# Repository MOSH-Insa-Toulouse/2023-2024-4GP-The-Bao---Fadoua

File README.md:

# 2023-2024-4GP-The-Bao---Fadoua

# 1. Description du projet  
Notre projet, inscrit dans l'UF "Du capteur au banc de test en open source hardware" de la 4ème année de Génie Physique à l’INSA Toulouse, vise à concevoir, fabriquer et caractériser un capteur de contrainte innovant utilisant une approche low-tech basée sur des capteurs en graphite. S'inspirant des travaux de chercheurs dans le domaine des capteurs, notre objectif est de développer un système de mesure complet, intégrant un shield Arduino avec un circuit analogique incluant un amplificateur transimpédance et des filtres, ainsi qu'une interface utilisateur via un écran OLED et une communication sans fil avec une application Android via un module Bluetooth. Nous avons également créé un banc de test pour évaluer les performances du capteur, en mesurant sa variation de résistance en fonction de la déformation induite par différents crayons graphites. Ces travaux aboutiront à la rédaction d'une datasheet détaillée du capteur, offrant ainsi une solution open source pour la mesure de contraintes basée sur une approche low-tech.

# 2. Livrables 
Les livrables de ce projet sont les suivants :
  
* Circuit Shield PCB avec Arduino UNO
     
   - Schéma électrique du circuit amplificateur transimpédance
   - Conception du PCB réalisée sous KiCad
   - Fabrication du PCB et soudure des composants
   - Intégration des éléments : amplificateur, module Bluetooth, écran OLED, encodeur rotatif
  
* Code Arduino     
   - Développement complet d'un code Arduino pour le fonctionnement du système.
   -  Fonctionnalités incluses :
   - Mesure de la déformation du capteur à base de graphite.
   -Transmission des données via le module Bluetooth.
   - Affichage des mesures sur l'écran OLED.
   - Utilisation de l'encodeur rotatif pour naviguer dans le menu de l'OLED.
  
* Application Android (APK)
* Banc de Test Dédié au Capteur
*  Datasheet Complète du Capteur
 ## 3. Matériel nécessaire
* Carte Arduino UNO
* Amplificateur opérationnel (LTC1050)
* Module Bluetooth (HC-05)
* Écran OLED
* Encodeur rotatif (KY-040)
* Flex Sensor
* 2 Résistance de 100kΩ
* 1 Résistance de 1kΩ
* 1 Résistance de 10kΩ
* Potentiomètre digital MCP-41050
* 2 Condensateurs 100nF
* 1 Condensateurs 1µF

 # 4. Electronique Analogique:
 
Le circuit amplificateur transimpédance est une composante essentielle de notre projet, car il permet de convertir le courant provenant du capteur de déformation à base de graphite en une tension mesurable. Composé de plusieurs éléments interagissant de manière précise, ce circuit garantit des mesures fiables et précises tout au long du processus.

Au cœur du circuit se trouve l'amplificateur opérationnel LTC1050, auquel le capteur de déformation est connecté à l'entrée inverseuse. Ce capteur, conçu pour ajuster sa résistance en fonction de la déformation, induit ainsi un changement de courant à travers la résistance de rétroaction R1.

La précision de nos mesures est assurée par le choix du LTC1050 pour ses faibles valeurs d'offset et de dérive. En complément, nous avons intégré trois étages de filtres au circuit pour optimiser le signal. Un filtre passe-bas à l'entrée (R1,C1) de 16 Hz atténue les hautes fréquences indésirables. Un second filtre passe-bas (R4, C2) de 1,6 Hz élimine le bruit de 50 Hz du réseau électrique. Enfin, un filtre final (R5,C3) de 1,6 kHz traite le bruit de l'ADC pour garantir des mesures précises et stables.

Chaque composant du circuit a été soigneusement sélectionné et dimensionné pour optimiser les performances. Des simulations approfondies sous LTSpice ont validé le fonctionnement du circuit avant la conception du PCB final. Des tests sur une breadboard ont confirmé sa fiabilité en conditions réelles, avec des mesures de résistance et de déformation du capteur réalisées pour évaluer sa précision.

La formule utilisée pour calculer la résistance du capteur de contrainte au graphite est la suivante :

      𝑅𝑠𝑒𝑛𝑠𝑜𝑟 = (1 +𝑅4/𝑅2) ∗ 𝑅1 ∗ (𝑉𝐶𝐶/𝑉𝐴𝐷𝐶) − 𝑅1 − 𝑅3

<h2> Modélisation du capteur:
     
</br>

<h2> Voici le schéma du circuit simulé sur le logiciel LTSpice :

</br>

 # 5. Progamme Arduino:
 Notre programme d'Arduino nous permet de mesurer la résistance des deux capteurs (Flex sensor et Capteur en graphine) à partir de la valeur tension mesuré par la composant ADC dans l'Arduino. Il affiche ensuite sur l'écran OLED les valeurs de résistance sélectionnées en tournant l'encodeur rotatoire. 

Dans notre programme, on a également établi la connexion entre la module bluetooth et l'application mobile. C'est à dire qu'on a créé les protocols de communication entre eux. Vous pouvez voir dans le diagramme ci-dessous que le module Bluetooth est utilisé pour recevoir les commandes de l'application mobile et lui envoyer les données demandées. L'Arduino va recevoir ces commandes pour envoyer des données à l'application mobile ou régler la résistance du potentiomètre numérique afin de changer le gain de l'amplificateur. 

 # 6. KiCad:
 ## Réalisation de la Schématique de Shield
Dans cette étape de réalisation de la schématique du shield, notre objectif principal était de concevoir un circuit électronique fonctionnel pour notre projet. Nous avons choisi le logiciel KiCad comme plateforme de conception et nous nous sommes basés sur le modèle d'une carte Arduino Uno pour assurer la compatibilité. Après avoir identifié tous les composants nécessaires pour notre projet, nous avons ensuite procédé à la création de notre propre bibliothèque d'empreintes personnalisées pour les composants manquants. Cette démarche nous a permis d'adapter notre conception à nos besoins spécifiques et d'assurer une intégration optimale des composants dans notre schéma électrique.
Voici les symboles et empreintes des composants que nous avons créés dans le logiciel KiCad :

### **Module Bluetooth (HC-05)**
  
<div class="column" align="center">

</div>

### **Encodeur rotatif (KY-040)**
<div class="column" align="center">

</div>

### **Écran OLED**
<div class="column" align="center"> 

</div>

### **Flex Sensor**
  <div class="column" align="center">

</div>

###  **Potentiomètre digital MCP-41050**

<div class="column" align="center">

</div>

Après avoir créé les schémas et les empreintes pour chaque composant, nous avons assemblé le schéma électrique complet du shield Arduino en reliant les broches des composants avec celles de la carte Arduino.

<div class="column" align="center">

</div>

### Réalisation de la Schématique du PCB et visualisation 3D
Dans cette étape, nous avons réalisé le routage de notre circuit en intégrant les composants sur le PCB, tout en veillant à limiter les distances entre les composants et leurs pins, conformément aux directives de nos enseignants référents, M. Jérémie Grisolia et Mme Catherine Crouzet. Nous avons respecté des paramètres spécifiques tels que la largeur des pistes, la largeur d'isolation des pistes et les dimensions des trous pour chaque composant, afin d'assurer la conformité de notre conception. Une fois cette phase terminée, nous avons ajouté le plan de masse pour relier les pistes au GND.

Les paramètres spécifiques suivants ont été respectés :
* Taille du trou de perçage pour l'écran OLED,Flex Sensor,le module Bluetooth et l'encodeur rotatoire, l'AOP et le potentiomètre digital = 1mm
* Taille du trou de perçage pour les résistances et les capacités = 0.8 mm
* Dimensions du trou pour le support de l'AOP ,l'écran OLED,Flex Sensor,le module Bluetooth et l'encodeur rotatoire,le potentiomètre digital (pad n°1 rectangulaire et les autres pins sont ovales) = 2 mm * 2.5 mm
* Largeur d'isolation des pistes = 0.8 mm
* Taille du trou de perçage du via = 0.8 mm

### **Visualisation 3D**
  
Après avoir réalisé le PCB, le téléchargement des modèles de composants sur le site "grabcad.com", qui n'étaient pas fournis par KiCad, s'est avéré très utile. Cela nous a permis d'obtenir un modèle 3D de notre PCB final. Nous avons ainsi pu vérifier que les positions des composants étaient correctes avant de passer à l'étape de l'impression du circuit.

### **Fabrication du shield PCB:**
  
Dans le cadre de notre projet, nous avons fabriqué un circuit imprimé (PCB) au sein des départements de Génie Électrique et Informatique et de Génie Physique de l'INSA Toulouse. La fabrication a commencé par la modélisation du circuit sur le logiciel KICAD, suivie de l'impression de cette modélisation sur du papier calque. Nous avons ensuite réalisé une insolation UV de notre plaquette d’époxy recouverte d’une fine couche de cuivre (environ 60 µm) pendant une dizaine de minutes, en utilisant le calque comme masque. La résine non exposée aux UV a été retirée avec un révélateur, puis la plaquette a été plongée dans un bain de perchlorure de fer pendant environ 7 à 9 minutes. Cette étape a permis de dissoudre le cuivre non protégé et de révéler les pistes du circuit. Enfin, un rinçage à l'acétone a été effectué pour éliminer les dernières traces de résine, nous permettant ainsi d'obtenir notre PCB conforme à la modélisation initiale. Cette réalisation a été possible grâce à l'aide précieuse de Cathy, assurant la qualité et la précision du produit final.

<div class="column" align="center">

 </div>

### Assemblage des composantes :
Une fois le PCB fabriqué, nous avons procédé à l'assemblage des composants, ce qui implique le perçage du PCB et la soudure des éléments électroniques. Conformément aux spécifications de notre projet, deux tailles de trous ont été prévues dans la conception sur KICAD : des trous de 0,8 mm de diamètre pour les composants tels que les amplificateurs opérationnels (AOP) LTC1050, les résistances et les capacités, et des trous de 1 mm de diamètre pour les broches de connexion de la carte Arduino Uno et les headers des différents modules (OLED, Bluetooth, encodeur rotatif...). À l'aide d'une perceuse électrique, nous avons percé le PCB aux emplacements désignés pour insérer les composants. Ensuite, nous avons soudé les composants en place en utilisant de l'étain pour assurer des connexions électriques solides et fiables. Ce processus d'assemblage a permis d'obtenir un shield opérationnel, prêt à être intégré dans notre système.

<div class="column" align="center">

</div>

 # 7. Application mobile:
Pour ce projet, nous avons développé une application mobile sur MIT App Inventor qui se connecte au module Bluetooth du capteur. Cette application dispose d'une interface unique permettant d'acquérir les données du capteur en temps réel, de les visualiser sur un graphique dynamique et de enregistrer le graphique dans notre téléphone ainsi que de régler le gain de l'amplificateur.

# Initilisation de programme:
<h3>Au début, nous avons déclaré les variable globale utilisé dans le programme de l'application

<br />

Initialiser le programme 

# Composantes dans l'interface:
## "Connect Device" 

Ce bouton est utilisé pour choisir la module bluetooth qu'on veut le connecter

## Statut de connexion bluetooth:
Étiquette représentant la statut de connexion Bluetooth. 

## "Disconnect" 
 Ce bouton est utilisé pour déconnecter la bluetooth.

## Zone graphique
 
On a utilisé la composante "Canvas" dans MIT pour visualiser le signal

Dans cette zone, le signal de tension mesuré est visualisé en fonction du temps. Chaque fois que le potentiel est mesuré, il est représenté par un point sur le graphique.

Concernant le fond du graphique, il est représenté en échelle linéaire. Chaque petit carré correspond à 500 ms en horizontale et à 0,25 V en verticale.

Figure 3: Le fond de la graphique

## Statut "Overload"

Parce que, l'Arduino ne mesure que jusqu'à 5V. En outre, avec un gain variable d'ampificatuer, la tension mesurée peut facilement devenir saturée. Ce phénomètre peut être observé lorsque le signal est visualisé dans la graphique. Pourtant, si on prendla valeur de résistance en seul fois, la saturation causerait un mal calcul de la résistance de capteur

Dans notre programme d'Arduino, nous avons défini une limitation de tension mesurée pour éviter la sarturation. La limitation de tension est 0 - 4.8V. Pour pouvoir détecter la saturation, une fois que la tension mesurée dépasse cette limite, l'Arduino vas envoyer un message qui contient une chaine des charactères "over". Si la message recus contien ce mot, l'étiquette "Overload" devient rouge; sinon, elle reste verte.

## "Start"
Lancer l'acquitiion de tension continue avec le délai entre deux acquisitions est 100ms

Une fois ce bouton est appuyé, il désactivera les boutons restants pour éviter d'être pressé par erreur et d'affecter l'acquisition. Pour arrêter l'acquisition, appuyez une nouvelle fois sur ce bouton.

Pour pouvoir récupérer automatiquement des données, nous commandons séquentiellement Arduino de nous evoyer les données. Pour cela, nous avons utilisé le composante "Clock"dans MIT

## "Step"
Ce bouton sert à récupérer la valeur de résistance du capteur sélectionné en une seule fois.

## "Save graph"

"En appuyant sur ce bouton, nous pouvons enregistrer le graphique dans le dossier "Photos" de notre téléphone au format .png. Pour cela, au début, on sauvegarde le graphe dans une mémoire externe de téléphone et nous le déplacons dans la dossier Photos de téléphone à l'aide d'extention "Taifuntool" 

## "Flex sensor" et "Graphite"
Ces boutons permettent de choisir le capteur dont on veut afficher la valeur.

## "Gain" Slider
Il utilisé pour régler le gain de l'amplificateur en changant la résistance de potentiomètre numérique. En utilisant ce curseurs, on peut choisir le gain qu'on souhaite. 

## "Change gain"

Un fois qu'on appuie sur ce bouton, on envoie un commande à l'Arduino pour changer le gain de l'amplificateur

## "Resistance Potentiometre"

Ce bouton sert à lire la résistance de potentiomètre

## "File Name" 

Ce composante est utilisé pour nommer la graphe qu'on va sauvegarder

 # 8. Mesures et résultats :
 
Pour étudier les caractéristiques du capteur, nous avons utilisé un banc d'essai composé de sept demi-cylindres disposés de manière séquentielle, du plus petit au plus grand. Le diamètre de chaque demi-cylindre variait de 2 cm à 5 cm, avec un pas de 0,5 cm.

Notre objectif était d'analyser la résistance du capteur en fonction de sa déformation induite en le pliant sur ces cylindres. Le degré de déformation a été calculé à l'aide de la formule  
 
      𝜀 = 𝑒 / (2r) 

Où **𝜀** représente la déformation, **e** désigne l'épaisseur de la feuille de papier, et **r** représente le rayon de chaque demi-cylindre. Pour l'épaisseur **e**, nous avons choisi une valeur de 0,16 mm, correspondant au grammage d'une feuille avec une densité de 140 g/m². 

Notre expérimentation a consisté à mesurer la déformation des capteurs sous compression et sous tension afin d'évaluer de manière exhaustive leurs caractéristiques de performance.

# 9. Remerciement et contact

Nous souhaiterions remercier Catherine Crouzet qui nous a beaucoup aidé à comprendre et à solutionner nos problèmes tout au long du projet. Nous adressons également nos remerciements à Jérémie Grisolia et Arnaud Biganzoli pour leur aide à la programmation Arduino et Github. 

Pour toutes questions ou informations supplémentaires, vous pouvez nous contacter par mail :

The Bao PHAM: pha@insatoulouse.fr
Fadoua EL GOURARI : elgourar@insa-toulouse.fr

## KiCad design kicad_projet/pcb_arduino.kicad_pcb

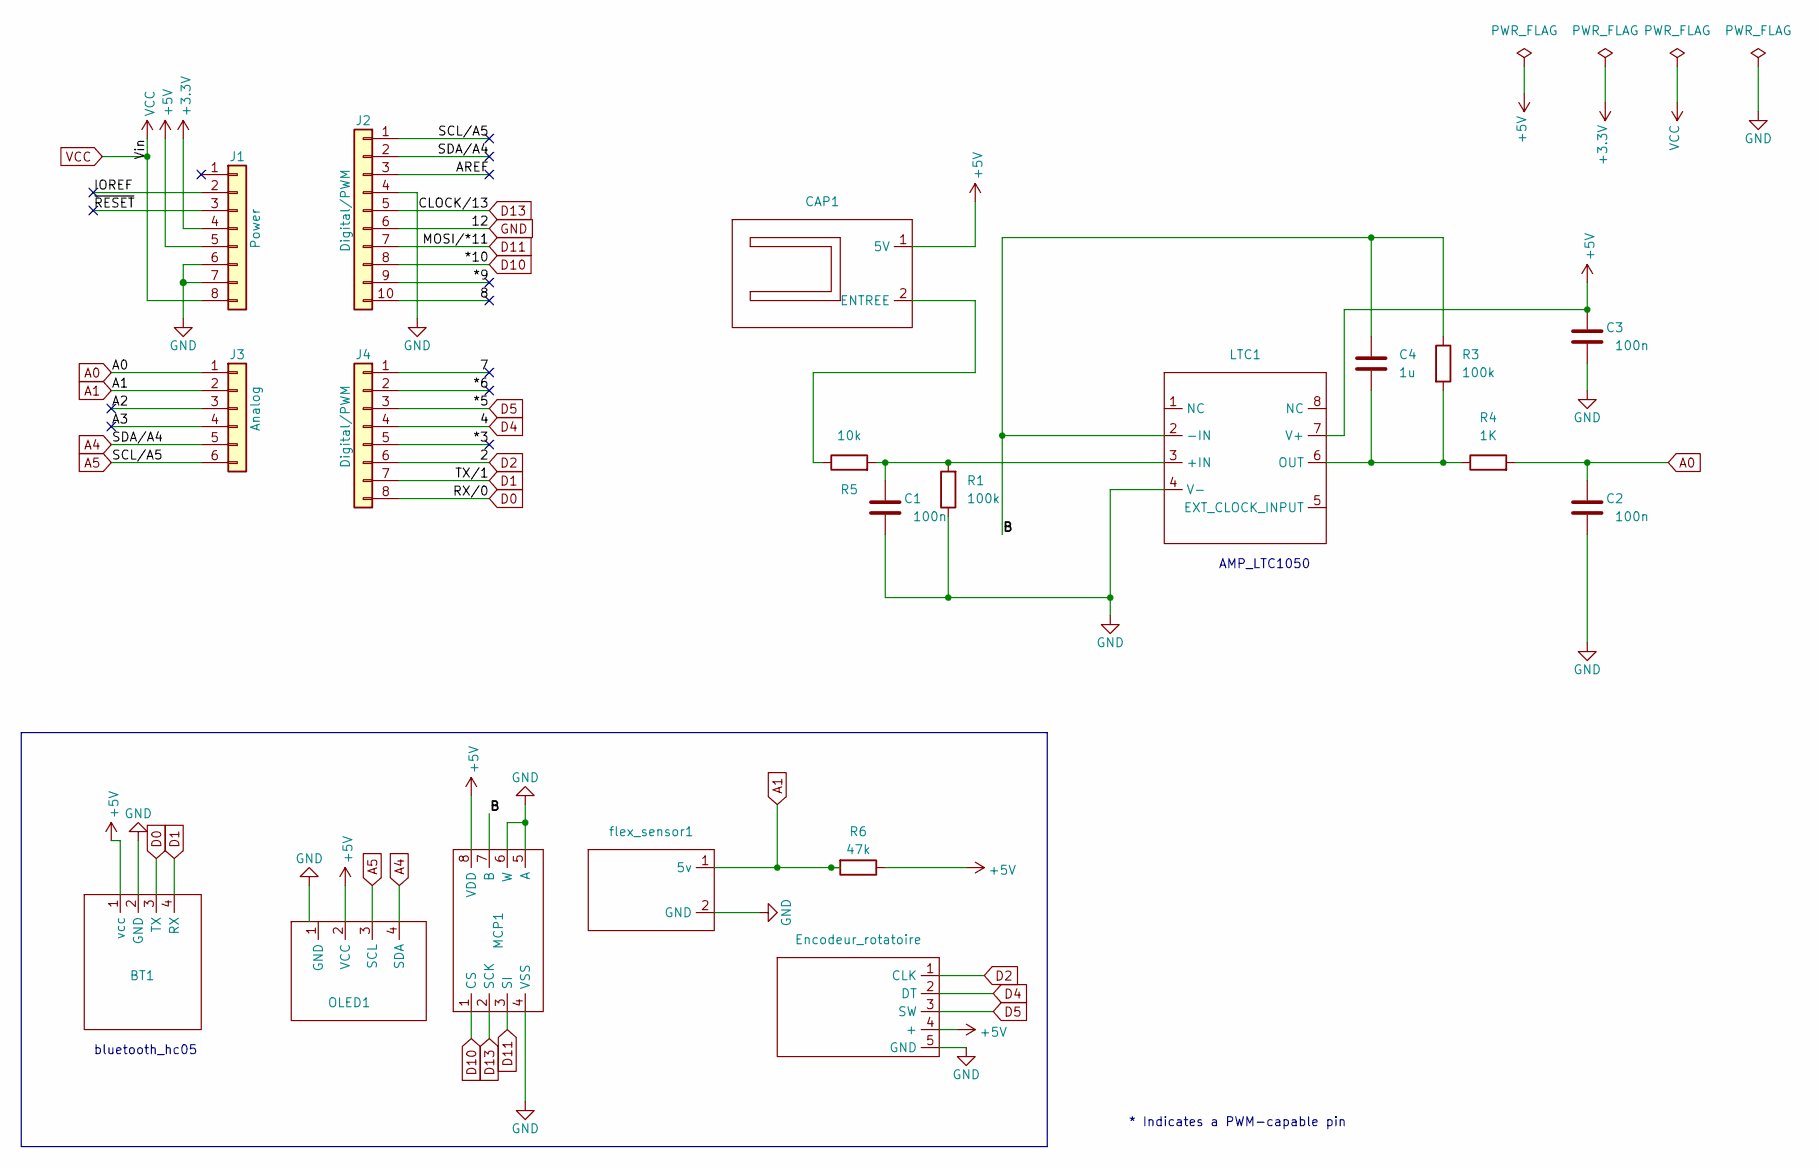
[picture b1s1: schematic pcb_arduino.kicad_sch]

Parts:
BT1: BT
C1, C2, C3: 100n; C_Disc_D4.3mm_W1.9mm_P5.00mm
C4: 1u; C_Rect_L7.2mm_W2.5mm_P5.00mm_FKS2_FKP2_MKS2_MKP2
CAP1: capteur
Encodeur_rotatoire: encodeur_rotatoire
J1: Power; PinSocket_1x08_P2.54mm_Vertical
J2: Digital/PWM; PinSocket_1x10_P2.54mm_Vertical
J3: Analog; PinSocket_1x06_P2.54mm_Vertical
J4: Digital/PWM; PinSocket_1x08_P2.54mm_Vertical
LTC1: LTC1050
MCP1: MCP41050
OLED1: OLED
R1, R3: 100k; R_Axial_DIN0207_L6.3mm_D2.5mm_P10.16mm_Horizontal
R4: 1K; R_Axial_DIN0207_L6.3mm_D2.5mm_P10.16mm_Horizontal
R5: 10k; R_Axial_DIN0207_L6.3mm_D2.5mm_P10.16mm_Horizontal
R6: 47k; R_Axial_DIN0207_L6.3mm_D2.5mm_P10.16mm_Horizontal
flex_sensor1: FLEX_SENSOR

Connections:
+3V3: J1.4
+5V: BT1.1 (vcc), C3.1, CAP1.1 (5V), Encodeur_rotatoire.4 (+), J1.5, LTC1.7 (V+), MCP1.8 (VDD), OLED1.2 (VCC), R6.1; also elsewhere on the board
/7: J4.1
/8: J2.10
/*3: J4.5
/*6: J4.2
/*9: J2.9
/A2: J3.3
/AREF: J2.3
/B: C4.1, LTC1.2 (-IN), MCP1.7 (B), R3.1
/IOREF: J1.2
/~RESET: J1.3
A0: C2.1, J3.1, R4.2
A1: J3.2, R6.2, flex_sensor1.1 (5v)
A4: J2.2, J3.5, OLED1.4 (SDA)
A5: J2.1, J3.6, OLED1.3 (SCL)
D0: BT1.3 (TX), J4.8
D1: BT1.4 (RX), J4.7
D2: Encodeur_rotatoire.1 (CLK), J4.6; also elsewhere on the board
D4: Encodeur_rotatoire.2 (DT), J4.4; also elsewhere on the board
D5: Encodeur_rotatoire.3 (SW), J4.3; also elsewhere on the board
D10: J2.8, MCP1.1 (CS)
D11: J2.7, MCP1.3 (SI)
D13: J2.5, MCP1.2 (SCK)
unnamed: CAP1.2 (ENTREE), R5.1
unnamed: C1.1, LTC1.3 (+IN), R1.2, R5.2
unnamed: C4.2, LTC1.6 (OUT), R3.2, R4.1
VCC: J1.8

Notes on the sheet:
bluetooth_hc05
* Indicates a PWM-capable pin
AMP_LTC1050

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
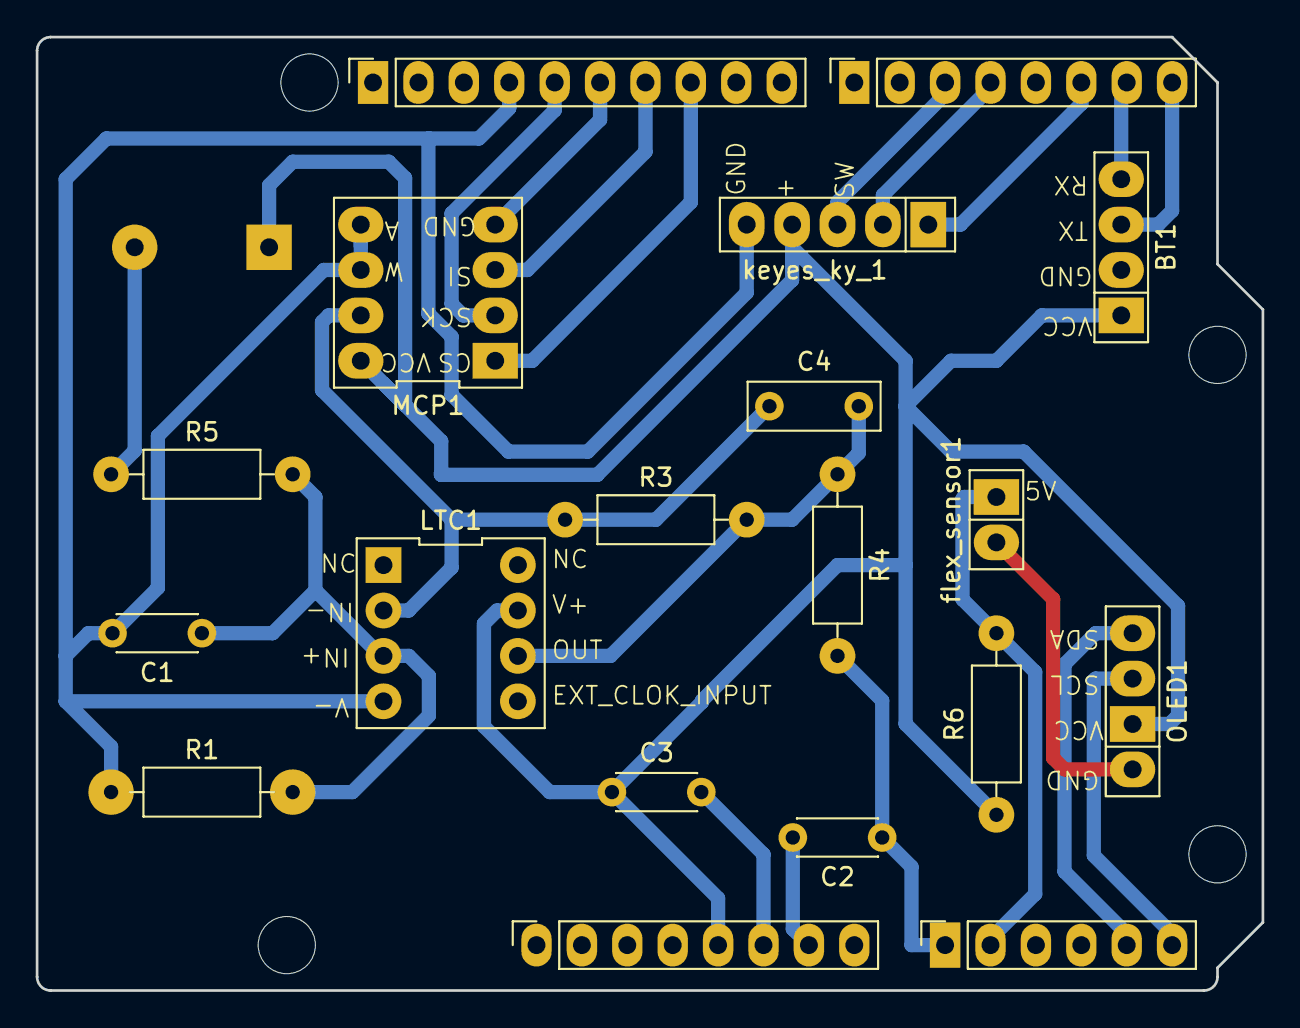
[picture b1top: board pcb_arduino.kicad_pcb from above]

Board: 2 copper layers, 68.6 x 53.3 mm, 24 parts (1 on the bottom side), 18 nets.

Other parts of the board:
MH1, MH2, MH3, MH4: MountingHole_3.2mm
keyes_ky_1: encodeur_rotatoire

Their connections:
+5V: keyes_ky_1.4 (+); also elsewhere on the board
D2: keyes_ky_1.1 (CLK); also elsewhere on the board
D4: keyes_ky_1.2 (DT); also elsewhere on the board
D5: keyes_ky_1.3 (SW); also elsewhere on the board

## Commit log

2024-03-12 1st version
2024-04-22 Arduino code
2024-04-22 Datasheet
2024-04-22 Datasheet 2version
2024-04-22 Kicad2
2024-04-22 Datasheet of LTC1050 and mcp41050
2024-04-22 Application
2024-04-22 Application structure
2024-04-22 Update README.md
    Ajouter les titres
2024-04-22 Update README.md
    Corriger
2024-04-22 Update README.md
    Corriger readme
2024-04-22 Update README.md
    change
2024-04-22 add image file
2024-04-22 Update README.md
    a
2024-04-22 Update README.md
    add images
2024-06-06 update The bao
2024-06-06 update application
2024-06-07 change
2024-06-07 update datasheet
2024-06-07 update 3d model
2024-06-07 update graphe
